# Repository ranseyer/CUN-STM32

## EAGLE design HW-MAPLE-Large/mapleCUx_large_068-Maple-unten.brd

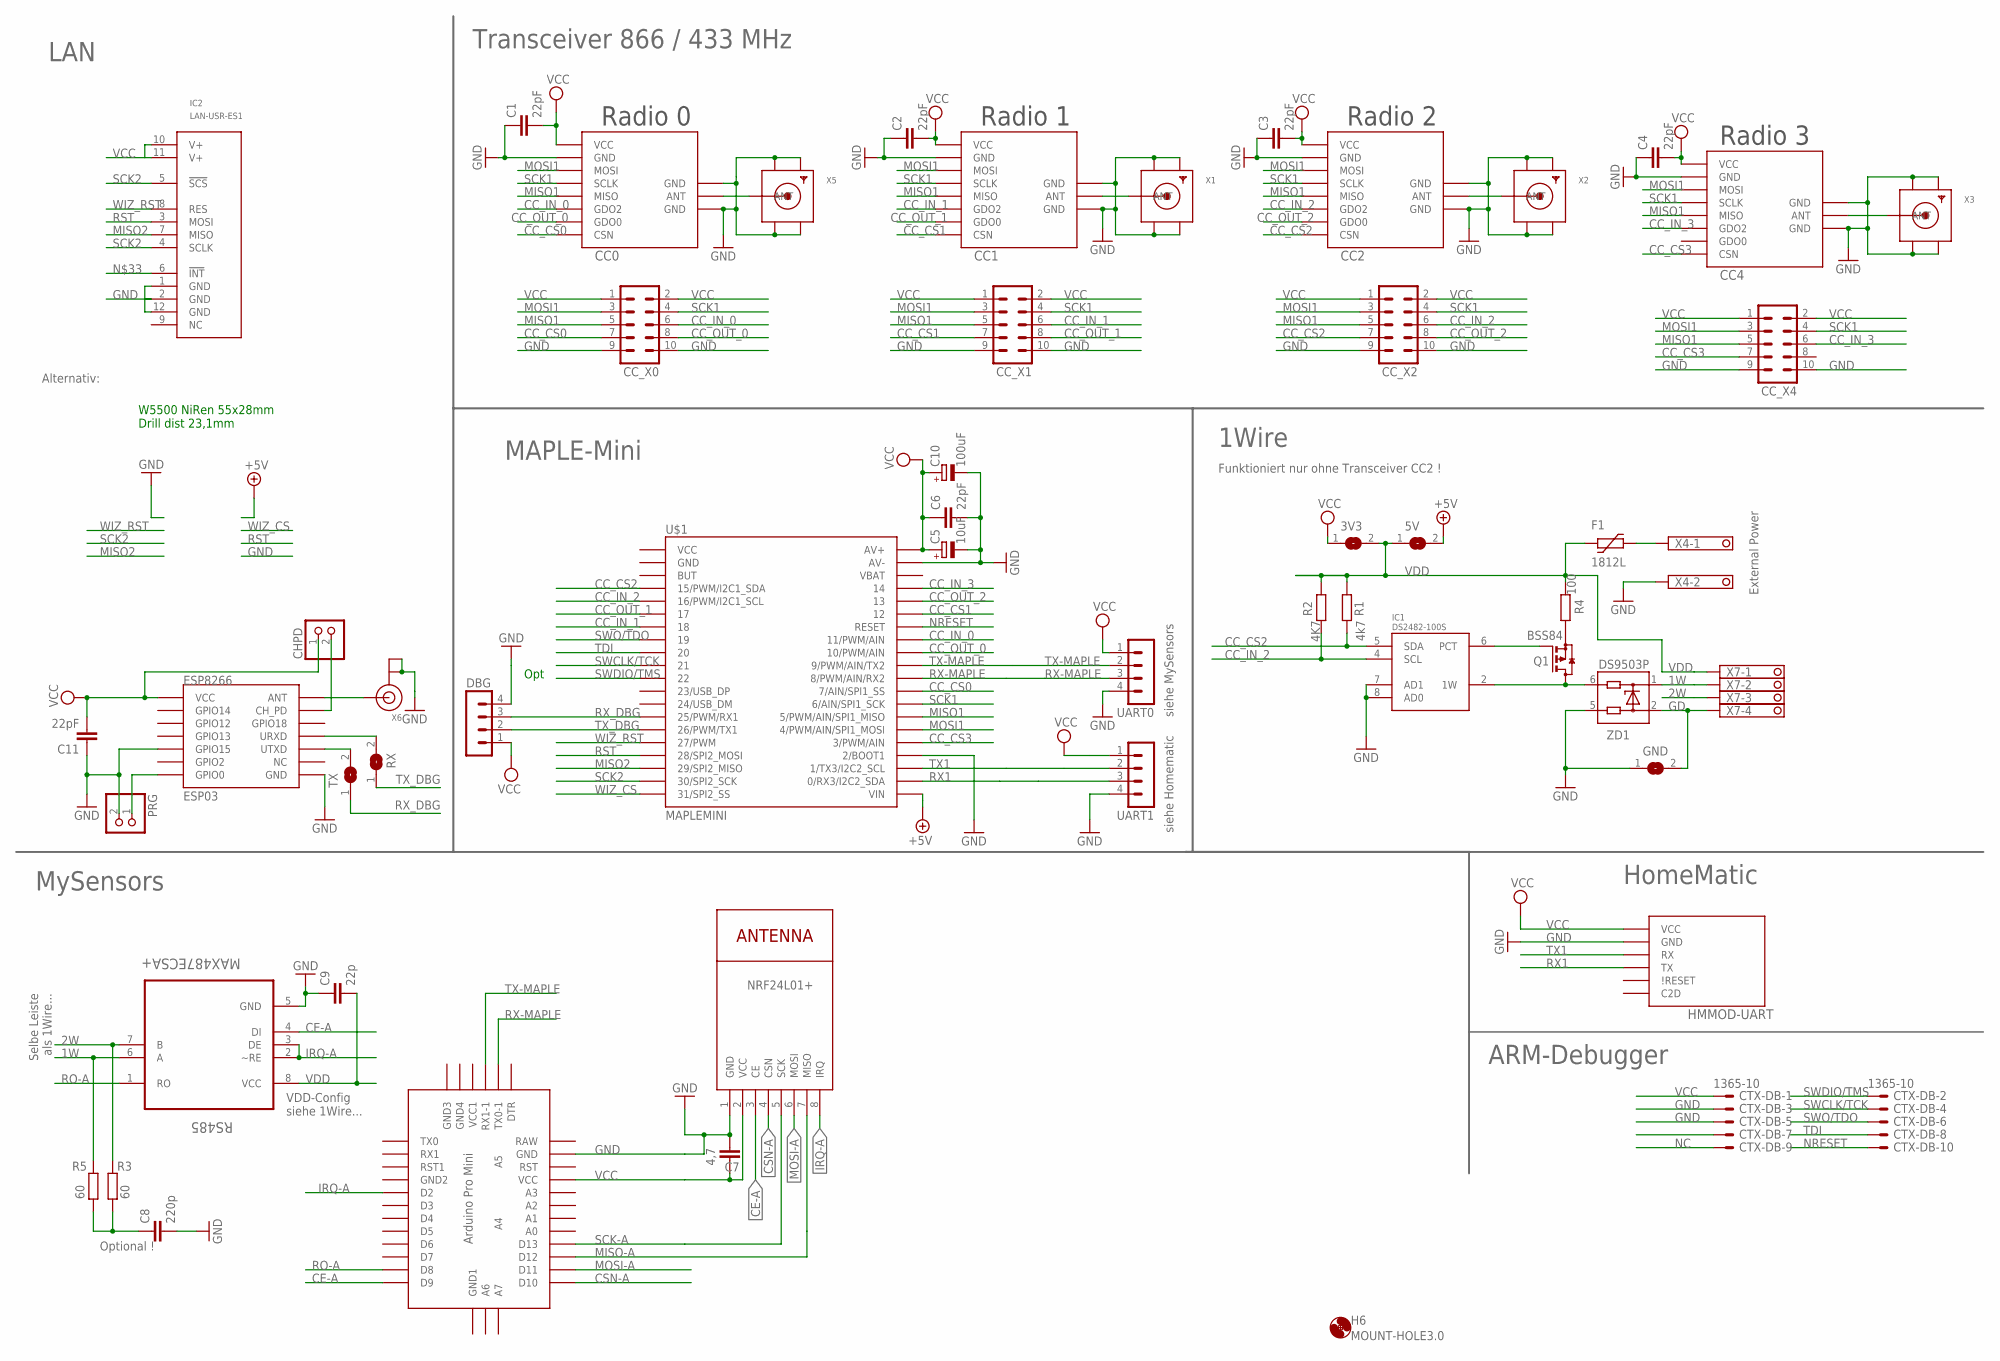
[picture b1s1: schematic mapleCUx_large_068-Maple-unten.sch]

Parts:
3V3, 5V: SJ
C1, C2, C3, C4, C6, C11: 22pF; C0805
C5: 10uF; R/2012-12W
C7: 4,7; C1210
C8: 220p; C0805
C9: 22p; C0805
C10: 100uF; E5-8,5
CC0: CC1101; CC1101_MODULE1_SMD
CC1, CC2, CC4: CC1101_MODULE1SMD; CC1101_MODULE1_SMD
CC_X0, CC_X1, CC_X2, CC_X4: MA05-2
CHPD: PINHD-1X2; 1X02
CTX-DB: 1365-10
DBG: MA04-1
ESP8266: ESP03
F1: 1812L
GND: SJ
H6: MOUNT-HOLE3.0; 3,0
HMMOD-UART: HM-MOD-UARTDIL; HM-MOD-UART-DIL
IC1: DS2482-100S; SO08
IC2: LAN-USR-ES1; USR-ES1
NRF24L01+: NRF24L01+; WIRELESS-NRF24L01
PRG: PINHD-1X2; 1X02
Q1: BSS84; SOT23
R1: 4k7; R0805
R2: 4K7; R0805
R3, R5: 60; R0805
R4: 100; R0805
RS485: MAX487ECSA+; SOIC127P600X175-8N
RX: SJ
TX: SJ
U$1: MAPLEMINI; 20-DIP
U$2: ABK-PRO-MINI
UART0, UART1: MA04-1
X1, X2, X3, X5: SMACONNECTOR_EDGE_UFL; SMA_EDGELAUNCH_UFL
X4: 1751248
X6: ANTENNA_U.FL; U.FL
X7: 1751264
ZD1: DS9503P; TSOC6

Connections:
1W: R5.2, RS485.6 (A), X7.2, ZD1.1
2W: R3.2, RS485.7 (B), X7.3
+5V: 5V.2, U$1.21 (VIN)
CC_CS0: CC0.CSN, CC_X0.7, U$1.29 (7/AIN/SPI1_SS)
CC_CS1: CC1.CSN, CC_X1.7, U$1.35 (12)
CC_CS2: CC2.CSN, CC_X2.7, IC1.5 (SDA), R1.2, U$1.4 (15/PWM/I2C1_SDA)
CC_CS3: CC4.CSN, CC_X4.7, U$1.25 (3/PWM/AIN)
CC_IN_0: CC0.GDO2, CC_X0.6, U$1.33 (11/PWM/AIN)
CC_IN_1: CC1.GDO2, CC_X1.6, U$1.7 (18)
CC_IN_2: CC2.GDO2, CC_X2.6, IC1.4 (SCL), R2.2, U$1.5 (16/PWM/I2C1_SCL)
CC_IN_3: CC4.GDO2, CC_X4.6, U$1.37 (14)
CC_OUT_0: CC0.GDO0, CC_X0.8, U$1.32 (10/PWM/AIN)
CC_OUT_1: CC1.GDO0, CC_X1.8, U$1.6 (17)
CC_OUT_2: CC2.GDO0, CC_X2.8, U$1.36 (13)
CE-A: NRF24L01+.3 (CE), RS485.4 (DI), U$2.D9
CSN-A: NRF24L01+.4 (CSN), U$2.D10
GD: GND.2, X7.4, ZD1.2
GND: C1.1, C2.1, C3.1, C4.1, C5.-, C6.2, C7.1, C8.2, C9.1, C10.-, C11.1, CC0.GND@0 (GND), CC0.GND@1 (GND), CC0.GND@2 (GND), CC1.GND@0 (GND), CC1.GND@1 (GND), CC1.GND@2 (GND), CC2.GND@0 (GND), CC2.GND@1 (GND), CC2.GND@2 (GND), CC4.GND@0 (GND), CC4.GND@1 (GND), CC4.GND@2 (GND), CC_X0.9, CC_X0.10, CC_X1.9, CC_X1.10, CC_X2.9, CC_X2.10, CC_X4.9, CC_X4.10, CTX-DB.3, CTX-DB.5, DBG.4, ESP8266.GND, ESP8266.GPIO15, GND.1, HMMOD-UART.2 (GND), IC1.3 (GND), IC1.7 (AD1), IC1.8 (AD0), IC2.1 (GND), IC2.2 (GND), IC2.12 (GND), NRF24L01+.1 (GND), PRG.2, RS485.5 (GND), U$1.24 (2/BOOT1), U$1.39 (AV-), U$2.GND, UART0.4, UART1.4, X1.GND@1 (GND1), X1.GND@2 (GND2), X1.GND@3 (GND3), X1.GND@4 (GND4), X2.GND@1 (GND1), X2.GND@2 (GND2), X2.GND@3 (GND3), X2.GND@4 (GND4), X3.GND@1 (GND1), X3.GND@2 (GND2), X3.GND@3 (GND3), X3.GND@4 (GND4), X4.2, X5.GND@1 (GND1), X5.GND@2 (GND2), X5.GND@3 (GND3), X5.GND@4 (GND4), X6.1 (GND), X6.2 (GND), ZD1.5
IRQ-A: NRF24L01+.8 (IRQ), RS485.2 (~RE), RS485.3 (DE), U$2.D2
MISO1: CC0.MISO, CC1.MISO, CC2.MISO, CC4.MISO, CC_X0.5, CC_X1.5, CC_X2.5, CC_X4.5, U$1.27 (5/PWM/AIN/SPI1_MISO)
MISO2: IC2.7 (MISO), U$1.18 (29/SPI2_MISO)
MISO-A: NRF24L01+.7 (MISO), U$2.D12
MOSI1: CC0.MOSI, CC1.MOSI, CC2.MOSI, CC4.MOSI, CC_X0.3, CC_X1.3, CC_X2.3, CC_X4.3, U$1.26 (4/PWM/AIN/SPI1_MOSI)
MOSI-A: NRF24L01+.6 (MOSI), U$2.D11
unnamed: CC1.ANT, X1.P (ANT)
unnamed: CC4.ANT, X3.P (ANT)
unnamed: CC2.ANT, X2.P (ANT)
unnamed: CC0.ANT, X5.P (ANT)
unnamed: ESP8266.GPIO0, PRG.1
unnamed: ESP8266.ANT, X6.3 (SIGNAL)
unnamed: CHPD.2, ESP8266.CH_PD
unnamed: ESP8266.URXD, RX.2
unnamed: ESP8266.UTXD, TX.2
unnamed: C8.1, R3.1, R5.1
unnamed: F1.P$2 (2), X4.1
unnamed: IC1.6 (PCT), Q1.1 (G)
unnamed: IC1.2 (1W), Q1.3 (D), ZD1.6
unnamed: Q1.2 (S), R4.1
NC: CTX-DB.9
NRESET: CTX-DB.10, U$1.34 (RESET)
RO-A: RS485.1 (RO), U$2.D8
RST: IC2.3 (MOSI), U$1.17 (28/SPI2_MOSI)
RX1: HMMOD-UART.5 (TX), U$1.22 (0/RX3/I2C2_SDA), UART1.3
RX-MAPLE: U$1.30 (8/PWM/AIN/RX2), U$2.TX0-1, UART0.3
RX_DBG: DBG.3, TX.1, U$1.14 (25/PWM/RX1)
SCK1: CC0.SCLK, CC1.SCLK, CC2.SCLK, CC4.SCLK, CC_X0.4, CC_X1.4, CC_X2.4, CC_X4.4, U$1.28 (6/AIN/SPI1_SCK)
SCK2: IC2.4 (SCLK), IC2.5 (!SCS!), U$1.19 (30/SPI2_SCK)
SCK-A: NRF24L01+.5 (SCK), U$2.D13
SWCLK/TCK: CTX-DB.4, U$1.10 (21)
SWDIO/TMS: CTX-DB.2, U$1.11 (22)
SWO/TDO: CTX-DB.6, U$1.8 (19)
TDI: CTX-DB.8, U$1.9 (20)
TX1: HMMOD-UART.6 (RX), U$1.23 (1/TX3/I2C2_SCL), UART1.2
TX-MAPLE: U$1.31 (9/PWM/AIN/TX2), U$2.RX1-1, UART0.2
TX_DBG: DBG.2, RX.1, U$1.15 (26/PWM/TX1)
VCC: 3V3.1, C1.2, C2.2, C3.2, C4.2, C5.+, C6.1, C7.2, C10.+, C11.2, CC0.VCC, CC1.VCC, CC2.VCC, CC4.VCC, CC_X0.1, CC_X0.2, CC_X1.1, CC_X1.2, CC_X2.1, CC_X2.2, CC_X4.1, CC_X4.2, CHPD.1, CTX-DB.1, DBG.1, ESP8266.VCC, HMMOD-UART.1 (VCC), IC2.10 (V+), IC2.11 (V+), NRF24L01+.2 (VCC), U$1.40 (AV+), U$2.VCC, UART0.1, UART1.1
VDD: 3V3.2, 5V.1, C9.2, F1.P$1 (1), IC1.1 (VDD), R1.1, R2.1, R4.2, RS485.8 (VCC), X7.1
WIZ_CS: U$1.20 (31/SPI2_SS)
WIZ_RST: IC2.8 (RES), U$1.16 (27/PWM)

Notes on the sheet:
Radio 1
Radio 0
Opt
Radio 2
Radio 3
W5500 NiRen 55x28mm Drill dist 23,1mm
siehe Homematic
siehe MySensors
1Wire
MySensors
HomeMatic
MAPLE-Mini
Transceiver 866 / 433 MHz
LAN
External Power
Funktioniert nur ohne Transceiver CC2 !
Selbe Leiste als 1Wire...
VDD-Config siehe 1Wire...
ARM-Debugger
Optional !
Alternativ:

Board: 2 copper layers, 54 parts (20 on the bottom side), 57 nets, no tracks yet.

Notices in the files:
parts and their libraries:
diy-modules: Released under the Creative Commons Attribution 4.0 International License: http://creativecommons.org/licenses/by/4.0
